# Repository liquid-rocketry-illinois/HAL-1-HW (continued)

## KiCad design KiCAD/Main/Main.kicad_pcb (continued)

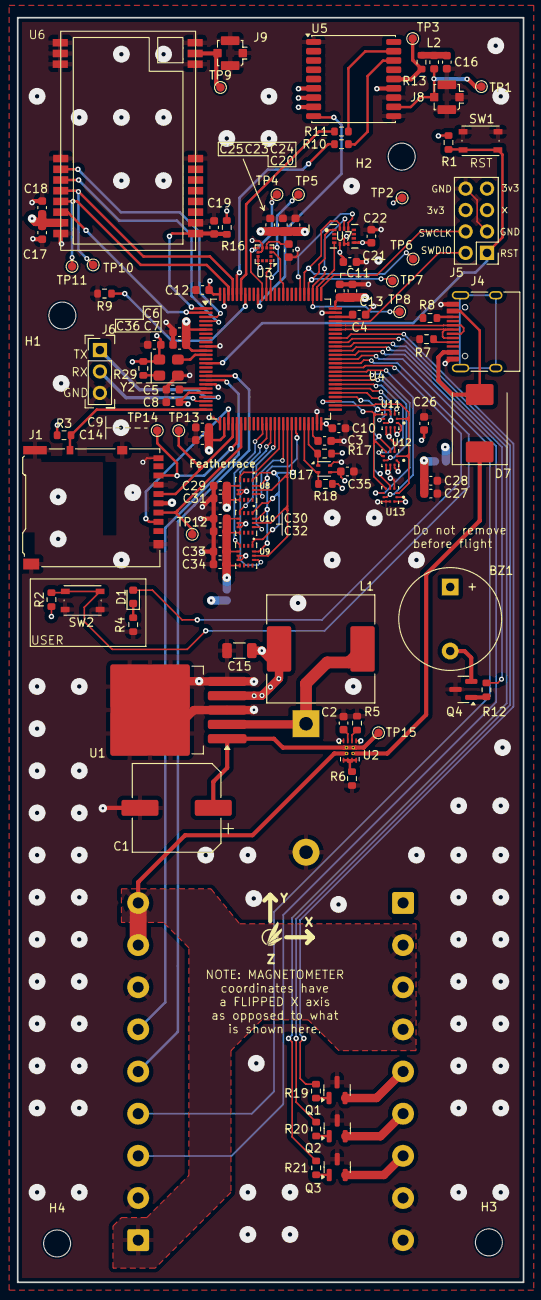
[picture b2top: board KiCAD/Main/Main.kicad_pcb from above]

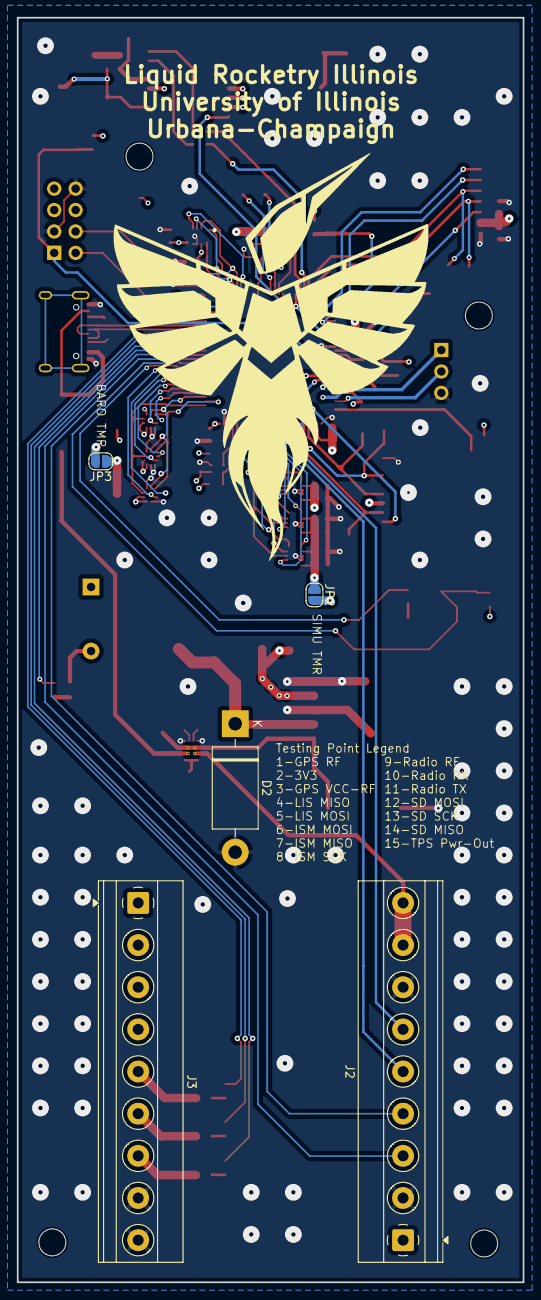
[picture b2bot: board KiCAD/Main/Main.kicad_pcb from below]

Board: 4 copper layers, 60.0 x 150.0 mm, 112 parts (5 on the bottom side), 96 nets.

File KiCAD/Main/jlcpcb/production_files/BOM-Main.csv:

Comment,Designator,Footprint,LCSC,Quantity
0.1u,C36,C_0603_1608Metric,C14663,1
10,"R13,R6",R_0603_1608Metric,C22859,2
100,R12,R_0603_1608Metric,C22775,1
100K,R2,R_0603_1608Metric,C25803,1
100N,C5,C_0603_1608Metric,C14663,1
100k,"R3,R5",R_0603_1608Metric,C25803,2
100n,"C10,C11,C12,C17,C19,C21,C22,C23,C25,C26,C27,C28,C29,C30,C31,C32,C33,C34,C35,C7,C8,C9",C_0603_1608Metric,C14663,22
10K,R1,R_0603_1608Metric,C25804,1
10k,"R16,R17,R18,R19,R20,R21,R9",R_0603_1608Metric,C25804,7
10n,"C16,C18,C2",C_0603_1608Metric,C57112,3
10u,C24,C_0603_1608Metric,C19702,1
1k,R29,R_0603_1608Metric,C21190,1
1u,"C13,C6",C_0603_1608Metric,C15849,2
2.2u,"C3,C4",C_0603_1608Metric,C23630,2
220n,C20,C_0603_1608Metric,C21120,1
220u,C15,C_1206_3216Metric,C412252,1
2N7002,Q4,SOT-23,C8545,1
33u,L1,L_SXN_SMDRI127,C9400,1
4.7u,C14,C_0603_1608Metric,C19666,1
47,"R10,R11",R_0603_1608Metric,C23182,2
47n,L2,L_0603_1608Metric,C29683,1
5.1k,"R7,R8",R_0603_1608Metric,C23186,2
634,R4,R_0603_1608Metric,C23094,1
680u,C1,CP_Elec_10x12.6,C976031,1
AO3400A,"Q1,Q2,Q3",SOT-23,C20917,3
BMP390L,"U11,U12,U13",XDCR_BMP390L,C2684802,3
Buzzer,BZ1,Buzzer_12x9.5RM7.6,C96093,1
Conn_Coaxial,"J8,J9",U.FL_Molex_MCRF_73412-0110_Vertical,C41432123,2
E22-900T22S,U6,E22-900T22S,C411289,1
Green 5mA,D1,LED_0603_1608Metric,C7371905,1
ISM6HG256x,U7,ISM6HG256XTR,C9900238913,1
LIS2MDL,U3,LGA-12_2x2mm_P0.5mm,C919695,1
LM2596S-3.3,U1,TO-263-5_TabPin3,C19631822,1
MAX-M10S,U5,ublox_MAX,C4153167,1
MBRS340,D7,D_SMC,C5338054,1
Micro_SD_Card_Det2,J1,microSD_HC_Hirose_DM3AT-SF-PEJM5,C9900222957,1
RESET,SW1,SW_Push_1P1T_NO_Vertical_Wuerth_434133025816,C843674,1
STM32H750VBTx,U4,LQFP-100_14x14mm_P0.5mm,C404010,1
SiT8008xx-2x-xxE (25MHz),Y2,Oscillator_SMD_SiT_PQFN-4Pin_3.2x2.5mm,C818511,1
TPS2121RUXR,U2,Texas_VQFN-HR-12_2x2.5mm_P0.5mm_ThermalVias,C485916,1
USB_C_Receptacle_USB2.0_16P,J4,USB_C_Receptacle_HRO_TYPE-C-31-M-12,C9900184415,1
USER,SW2,SW_Push_1P1T_NO_Vertical_Wuerth_434133025816,C843674,1
~,"U10,U8,U9",BMI323,C5368700,3

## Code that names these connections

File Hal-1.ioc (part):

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Mcu.Name=STM32H750VBTx
Mcu.Package=LQFP100
Mcu.UserName=STM32H750VBTx
PA0.Signal=UART4_TX
PA1.Signal=UART4_RX
PA11.GPIOParameters=GPIO_Label
PA11.GPIO_Label=USB D-
PA11.Mode=Device_Only
PA11.Signal=USB_OTG_FS_DM
PA12.GPIOParameters=GPIO_Label
PA12.GPIO_Label=USB D+
PA12.Mode=Device_Only
PA12.Signal=USB_OTG_FS_DP
PA13\ (JTMS/SWDIO).Mode=Serial_Wire
PA13\ (JTMS/SWDIO).Signal=DEBUG_JTMS-SWDIO
PA14\ (JTCK/SWCLK).Mode=Serial_Wire
PA14\ (JTCK/SWCLK).Signal=DEBUG_JTCK-SWCLK
PA15\ (JTDI).GPIOParameters=GPIO_Label
PA15\ (JTDI).GPIO_Label=ISM INT
PA15\ (JTDI).Signal=GPXTI15
PA3.GPIOParameters=GPIO_Label
PA3.GPIO_Label=SD_DET
PA3.Signal=GPIO_Input
PA4.GPIOParameters=GPIO_Label
PA4.GPIO_Label=CS1 [SD Card]
PA4.Signal=GPIO_Output
PA5.GPIOParameters=GPIO_Label
PA5.GPIO_Label=SCK6 [SD Card]
PA5.Mode=Full_Duplex_Master
PA5.Signal=SPI6_SCK
PA6.GPIOParameters=GPIO_Label
PA6.GPIO_Label=MISO6 [SD Card]
PA6.Mode=Full_Duplex_Master
PA6.Signal=SPI6_MISO
PA7.GPIOParameters=GPIO_Label
PA7.GPIO_Label=MOSI6 [SD Card]
PA7.Mode=Full_Duplex_Master
PA7.Signal=SPI6_MOSI
PA8.GPIOParameters=GPIO_Label
PA8.GPIO_Label=DROUGE_BACK
PA8.Signal=GPIO_Output
PA9.GPIOParameters=GPIO_Label
PA9.GPIO_Label=DROUGE_MAIN
PA9.Signal=GPIO_Output
PB10.GPIOParameters=GPIO_Label
PB10.GPIO_Label=SHT41 SCL
PB10.Mode=I2C
PB10.Signal=I2C2_SCL
PB11.GPIOParameters=GPIO_Label
PB11.GPIO_Label=SHT41 SDA
PB11.Mode=I2C
PB11.Signal=I2C2_SDA
PB13.GPIOParameters=GPIO_Label
PB13.GPIO_Label=SCK2 [BMP390]
PB13.Mode=Full_Duplex_Master
PB13.Signal=SPI2_SCK
PB14.GPIOParameters=GPIO_Label
PB14.GPIO_Label=MISO2 [BMP390]
PB14.Mode=Full_Duplex_Master
PB14.Signal=SPI2_MISO
PB15.GPIOParameters=GPIO_Label
PB15.GPIO_Label=MOSI2 [BMP390]
PB15.Mode=Full_Duplex_Master
PB15.Signal=SPI2_MOSI
PB2.GPIOParameters=GPIO_Label
PB2.GPIO_Label=INT3 [SIMU]
PB2.Signal=GPXTI2
PB3\ (JTDO/TRACESWO).GPIOParameters=GPIO_Label
PB3\ (JTDO/TRACESWO).GPIO_Label=SCK1 [Mag]
PB3\ (JTDO/TRACESWO).Signal=SPI1_SCK
PB4\ (NJTRST).GPIOParameters=GPIO_Label
PB4\ (NJTRST).GPIO_Label=MISO1 [Mag]
PB4\ (NJTRST).Signal=SPI1_MISO
PB5.GPIOParameters=GPIO_Label
PB5.GPIO_Label=GPS_RST
PB5.Signal=GPIO_Output
PB8.GPIOParameters=GPIO_Label
PB8.GPIO_Label=GPS I2CSCL
PB8.Mode=I2C
PB8.Signal=I2C4_SCL
PB9.GPIOParameters=GPIO_Label
PB9.GPIO_Label=GPS I2CSDA
PB9.Mode=I2C
PB9.Signal=I2C4_SDA
PC10.GPIOParameters=GPIO_Label
PC10.GPIO_Label=SCK3 [ISM]
PC10.Mode=Full_Duplex_Master
PC10.Signal=SPI3_SCK
PC11.GPIOParameters=GPIO_Label
PC11.GPIO_Label=MISO3 [ISM]
PC11.Mode=Full_Duplex_Master
PC11.Signal=SPI3_MISO
PC12.GPIOParameters=GPIO_Label
PC12.GPIO_Label=MOSI3 [ISM]
PC12.Mode=Full_Duplex_Master
PC12.Signal=SPI3_MOSI
PC2_C.GPIOParameters=GPIO_Label
PC2_C.GPIO_Label=SERVO1_ENC
PC2_C.Mode=IN0-Single-Ended
PC2_C.Signal=ADC3_INP0
PC3_C.GPIOParameters=GPIO_Label
PC3_C.GPIO_Label=SERVO2_ENC
PC3_C.Mode=IN1-Single-Ended
PC3_C.Signal=ADC3_INP1
PC6.GPIOParameters=GPIO_Label
PC6.GPIO_Label=SERVO2_PWM
PC6.Signal=S_TIM3_CH1
PC7.GPIOParameters=GPIO_Label
PC7.GPIO_Label=SERVO1_PWM
PC7.Signal=S_TIM3_CH2
PC8.GPIOParameters=GPIO_Label
PC8.GPIO_Label=BUZZER
PC8.Signal=S_TIM3_CH3
PC9.GPIOParameters=GPIO_Label
PC9.GPIO_Label=MAIN
PC9.Signal=GPIO_Output
PD0.GPIOParameters=GPIO_Label
PD0.GPIO_Label=CS ISM
PD0.Signal=GPIO_Output
PD10.GPIOParameters=GPIO_Label
PD10.GPIO_Label=CS2 [BMP390]
PD10.Signal=GPIO_Output
PD11.GPIOParameters=GPIO_Label
PD11.GPIO_Label=BMP390 INT2
PD11.Signal=GPXTI11
PD12.GPIOParameters=GPIO_Label
PD12.GPIO_Label=CS3 [BMP390]
PD12.Signal=GPIO_Output
PD13.GPIOParameters=GPIO_Label
PD13.GPIO_Label=BMP390 INT3
PD13.Signal=GPXTI13
PD14.GPIOParameters=GPIO_Label
PD14.GPIO_Label=USR_LED
PD14.Signal=GPIO_Output
PD15.GPIOParameters=GPIO_Label
PD15.GPIO_Label=USR_BUTTON
PD15.Signal=GPIO_Input
PD4.GPIOParameters=GPIO_Label
PD4.GPIO_Label=CS1 [Mag]
PD4.Signal=GPIO_Output
PD7.GPIOParameters=GPIO_Label
PD7.GPIO_Label=MOSI1 [Mag]
PD7.Signal=SPI1_MOSI
PD8.GPIOParameters=GPIO_Label
PD8.GPIO_Label=CS1 [BMP390]
PD8.Signal=GPIO_Output
PD9.GPIOParameters=GPIO_Label
PD9.GPIO_Label=BMP390 INT1
PD9.Signal=GPXTI9
PE0.GPIOParameters=GPIO_Label
PE0.GPIO_Label=RADIO_RX
PE0.Mode=Asynchronous
PE0.Signal=UART8_RX
PE1.GPIOParameters=GPIO_Label
PE1.GPIO_Label=RADIO_TX
PE1.Mode=Asynchronous
PE1.Signal=UART8_TX
PE10.GPIOParameters=GPIO_Label
PE10.GPIO_Label=INT1 [SIMU]
PE10.Signal=GPXTI10
PE11.GPIOParameters=GPIO_Label
PE11.GPIO_Label=CS1 [SIMU]
PE11.Signal=GPIO_Output
PE12.GPIOParameters=GPIO_Label
PE12.GPIO_Label=SCK4 [SIMU]
PE12.Mode=Full_Duplex_Master
PE12.Signal=SPI4_SCK
PE13.GPIOParameters=GPIO_Label
PE13.GPIO_Label=MISO4 [SIMU]
PE13.Mode=Full_Duplex_Master
PE13.Signal=SPI4_MISO
PE14.GPIOParameters=GPIO_Label
PE14.GPIO_Label=MOSI4 [SIMU]
PE14.Mode=Full_Duplex_Master
PE14.Signal=SPI4_MOSI
PE2.GPIOParameters=GPIO_Label
PE2.GPIO_Label=RADIO_RST
PE2.Signal=GPIO_Output
PE3.GPIOParameters=GPIO_Label
PE3.GPIO_Label=RADIO_AUX
PE3.Signal=GPIO_Output
PE4.GPIOParameters=GPIO_Label
PE4.GPIO_Label=M0_Radio
PE4.Signal=GPIO_Output
PE5.GPIOParameters=GPIO_Label
PE5.GPIO_Label=M1_Radio
PE5.Signal=GPIO_Output
PE7.GPIOParameters=GPIO_Label
PE7.GPIO_Label=CS3 [SIMU]
PE7.Signal=GPIO_Output
PE8.GPIOParameters=GPIO_Label
PE8.GPIO_Label=INT2 [SIMU]
PE8.Signal=GPXTI8
PE9.GPIOParameters=GPIO_Label
PE9.GPIO_Label=CS2 [SIMU]
PE9.Signal=GPIO_Output
PH0-OSC_IN\ (PH0).Mode=HSE-External-Clock-Source
PH0-OSC_IN\ (PH0).Signal=RCC_OSC_IN
RCC.SYSCLKFreq_VALUE=475000000
RCC.SYSCLKSource=RCC_SYSCLKSOURCE_PLLCLK
board=custom

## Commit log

2025-12-29 Complete layout first draft
2025-12-29 Changed out conenctor footprint for smaller, vertical THT component
2025-12-29 Marked components as ignored from board
2025-12-29 Moved custom footprints into local KiCAD footprint library
2025-12-29 Fixed footprints for terminal blocks
2025-12-30 It2 12-29-2025
2025-12-30 Moved MISO1 to better position
2025-12-30 Moved GPS I2C to more optimal location
2025-12-30 Fixed controller SCL/SDA pins
2025-12-30 Moved around some more pins for easier routing
2025-12-30 Initial component placement
2025-12-30 Changed debug header out for 2x4 to save space
2025-12-30 Changed BMM350 for LIS2MDL
2025-12-30 Fixed routing for LIS2MDL
2025-12-30 DRC and ground fills
2025-12-31 Layout and routing
2026-01-03 Arrange silkscreen & review
2026-01-07 Update aux magnetometer, test THs, and silkscreens
2026-01-08 Replace independent magnetometer, reformat test points, generate test gerber and BOM
2026-01-09 Update BOM and respective components according to LCSC supply, remove previously generated production files
2026-01-10 create servo test folder
2026-01-14 save progress
2026-01-14 save mid pcb-rev 01132026
2026-01-14 save after realizing branch was not switched to layoutv2
2026-01-15 Update datasheets and build theoretically working servo test code
2026-01-19 Edit PCB Layout to increase min hole size and decrease price, prepare production files, prepare for main branch merge
2026-01-19 Reorganize libraries into LRI.pretty, replace BMI270 with BMI323
2026-01-30 Upload (still) nonfunctional PWM for debug
2026-02-10 Add board mount part file
    temporary file that will be sorted/replaced later
2026-02-10 Add new CAD files for temporary upload
2026-02-11 Add add'l files from meeting
2026-02-11 Bring project up to date
2026-02-11 Organize prt files into folder
2026-02-15 Review CAD part 1
2026-02-15 Review CAD files part 2
2026-02-17 Add new KiCAD project for soldering practice board
2026-02-17 Write BMi260 explanations
2026-02-17 create lsm spi schematic for practice board
2026-02-17 create lsm spi practice board schematic
2026-02-17 Complete BMI260 Explanation
2026-02-17 Push reviewed CAD
2026-02-18 Add screw switch mounts, adjust top plate size
2026-02-19 Add antenna
2026-02-19 Extend screw switch thickness 4mm
2026-02-19 Add antenna constrainer
2026-02-19 Add spacer to top plate
2026-02-20 Add screw switch model and explode assembly
2026-02-24 Make LIS3 labels more concise
2026-02-24 copy mode 1 schematic for lsm
2026-03-03 Add BMP schematic
2026-03-03 Configure IOC file, rename pins
2026-03-03 create stl footprints
2026-03-03 begin stl pcb layout
2026-03-03 Define more mcu pins
